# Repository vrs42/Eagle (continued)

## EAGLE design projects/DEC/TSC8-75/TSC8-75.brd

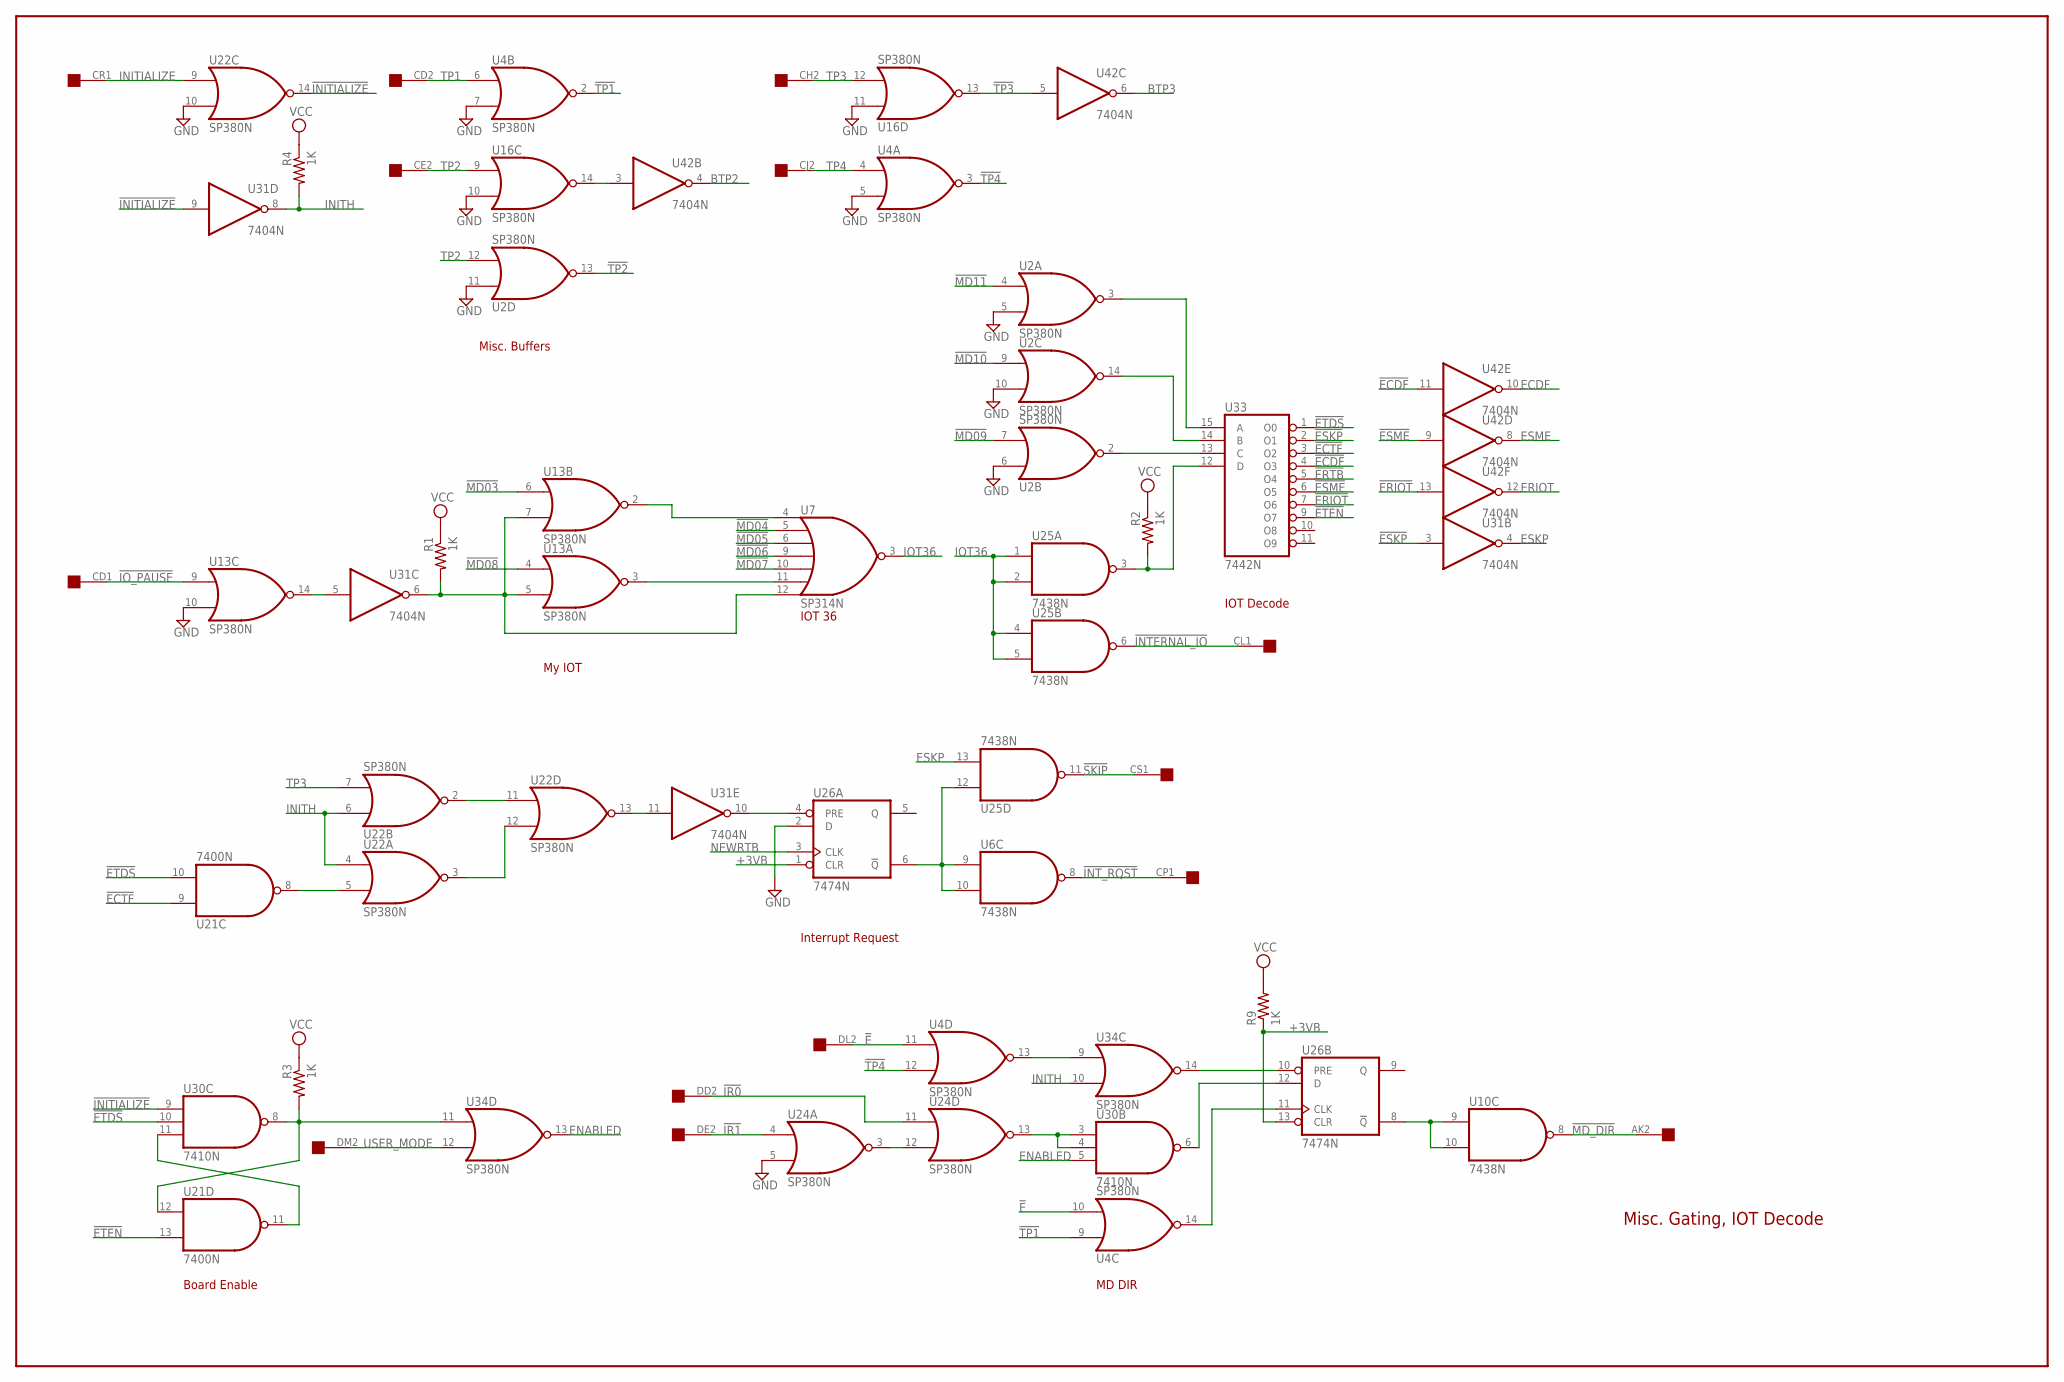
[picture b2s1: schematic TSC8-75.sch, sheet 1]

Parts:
EDGE: edge; EDGE-CON8
R1, R2, R3, R4, R9: 1K; 0204/7
U2, U4, U13, U16, U22, U24, U34: SP380N; DIL14
U6, U10, U25: 7438N; DIL14
U7: SP314N; DIL14
U21: 7400N; DIL14
U26: 7474N; DIL14
U30: 7410N; DIL14
U31, U42: 7404N; DIL14
U33: 7442N; DIL16

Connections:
!E: EDGE.DL2, U4.10 (I1), U4.11 (I0)
!ECDF: U33.4 (O3), U42.11 (I)
!ECTF: U21.9 (I0), U33.3 (O2)
!ERIOT: U33.7 (O6), U42.13 (I); also elsewhere on the board
!ERTB: U33.5 (O4); also elsewhere on the board
!ESKP: U31.3 (I), U33.2 (O1)
!ESME: U33.6 (O5), U42.9 (I)
!ETDS: U21.10 (I1), U30.10 (I1), U33.1 (O0); also elsewhere on the board
!ETEN: U21.13 (I1), U33.9 (O7)
!INITIALIZE: U22.14 (O), U30.9 (I0), U31.9 (I); also elsewhere on the board
!INTERNAL_IO: EDGE.CL1, U25.6 (O)
!INT_RQST: EDGE.CP1, U6.8 (O)
!IO_PAUSE: EDGE.CD1, U13.9 (I0)
!IR0: EDGE.DD2, U24.11 (I0)
!IR1: EDGE.DE2, U24.4 (I0)
!MD03: U13.6 (I0); also elsewhere on the board
!MD04: U7.5 (I1); also elsewhere on the board
!MD05: U7.6 (I2); also elsewhere on the board
!MD06: U7.9 (I3); also elsewhere on the board
!MD07: U7.10 (I4); also elsewhere on the board
!MD08: U13.4 (I0); also elsewhere on the board
!MD09: U2.7 (I1); also elsewhere on the board
!MD10: U2.9 (I0); also elsewhere on the board
!MD11: U2.4 (I0); also elsewhere on the board
!MD_DIR: EDGE.AK2, U10.8 (O)
!SKIP: EDGE.CS1, U25.11 (O); also elsewhere on the board
!TP1: U4.2 (O), U4.9 (I0)
!TP2: U2.13 (O); also elsewhere on the board
!TP3: U16.13 (O), U42.5 (I)
!TP4: U4.3 (O), U4.12 (I1)
+3VB: R9.1, U26.1 (CLR), U26.13 (CLR); also elsewhere on the board
BTP2: U42.4 (O); also elsewhere on the board
BTP3: U42.6 (O); also elsewhere on the board
ECDF: U42.10 (O); also elsewhere on the board
ENABLED: U30.5 (I2), U34.13 (O); also elsewhere on the board
ERIOT: U42.12 (O); also elsewhere on the board
ESKP: U25.13 (I1), U31.4 (O)
ESME: U42.8 (O); also elsewhere on the board
GND: U2.1 (GND), U2.5 (I1), U2.6 (I0), U2.10 (I1), U2.11 (I0), U4.1 (GND), U4.5 (I1), U4.7 (I1), U6.7 (GND), U7.1 (GND), U10.7 (GND), U13.1 (GND), U13.10 (I1), U16.1 (GND), U16.10 (I1), U16.11 (I0), U21.7 (GND), U22.1 (GND), U22.10 (I1), U24.1 (GND), U24.5 (I1), U25.7 (GND), U26.2 (D), U26.7 (GND), U30.7 (GND), U31.7 (GND), U33.8 (GND), U34.1 (GND), U42.7 (GND); also elsewhere on the board
INITH: R4.2, U22.4 (I0), U22.6 (I0), U31.8 (O), U34.10 (I1)
INITIALIZE: EDGE.CR1, U22.9 (I0)
IOT36: U7.3 (O), U25.1 (I0), U25.2 (I1), U25.4 (I0), U25.5 (I1)
IO_PAUSE: U13.14 (O), U31.5 (I)
IR1: U24.3 (O), U24.12 (I1)
IRQ: U6.9 (I0), U6.10 (I1), U25.12 (I0), U26.6 (!Q)
MD09H: U2.2 (O), U33.13 (C)
MD10H: U2.14 (O), U33.14 (B)
MD11H: U2.3 (O), U33.15 (A)
unnamed: U16.14 (O), U42.3 (I)
unnamed: U4.14 (O), U26.11 (CLK)
unnamed: U26.4 (PRE), U31.10 (O)
unnamed: U26.12 (D), U30.6 (O)
unnamed: U26.10 (PRE), U34.14 (O)
unnamed: U7.4 (I0), U13.2 (O)
unnamed: R1.2, U7.12 (I6), U13.5 (I1), U13.7 (I1), U31.6 (O)
unnamed: U7.11 (I5), U13.3 (O)
unnamed: R2.2, U25.3 (O), U33.12 (D)
unnamed: R3.2, U21.12 (I0), U30.8 (O), U34.11 (I0)
unnamed: U4.13 (O), U34.9 (I0)
unnamed: U24.13 (O), U30.3 (I0), U30.4 (I1)
unnamed: U22.2 (O), U22.11 (I0)
unnamed: U22.3 (O), U22.12 (I1)
unnamed: U21.8 (O), U22.5 (I1)
unnamed: U22.13 (O), U31.11 (I)
unnamed: U21.11 (O), U30.11 (I2)
unnamed: U10.9 (I0), U10.10 (I1), U26.8 (!Q)
NEWRTB: U26.3 (CLK); also elsewhere on the board
TP1: EDGE.CD2, U4.6 (I0)
TP2: EDGE.CE2, U2.12 (I1), U16.9 (I0)
TP3: EDGE.CH2, U16.12 (I1), U22.7 (I1)
TP4: EDGE.CJ2, U4.4 (I0)
USER_MODE: EDGE.DM2, U34.12 (I1); also elsewhere on the board
VCC: R1.1, R2.1, R3.1, R4.1, R9.2, U2.8 (VCC), U4.8 (VCC), U6.14 (VCC), U7.8 (VCC), U10.14 (VCC), U13.8 (VCC), U16.8 (VCC), U21.14 (VCC), U22.8 (VCC), U24.8 (VCC), U25.14 (VCC), U26.14 (VCC), U30.14 (VCC), U31.14 (VCC), U33.16 (VCC), U34.8 (VCC), U42.14 (VCC); also elsewhere on the board

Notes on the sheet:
IOT 36
Board Enable
My IOT
IOT Decode
MD DIR
Interrupt Request
Misc. Buffers
Misc. Gating, IOT Decode

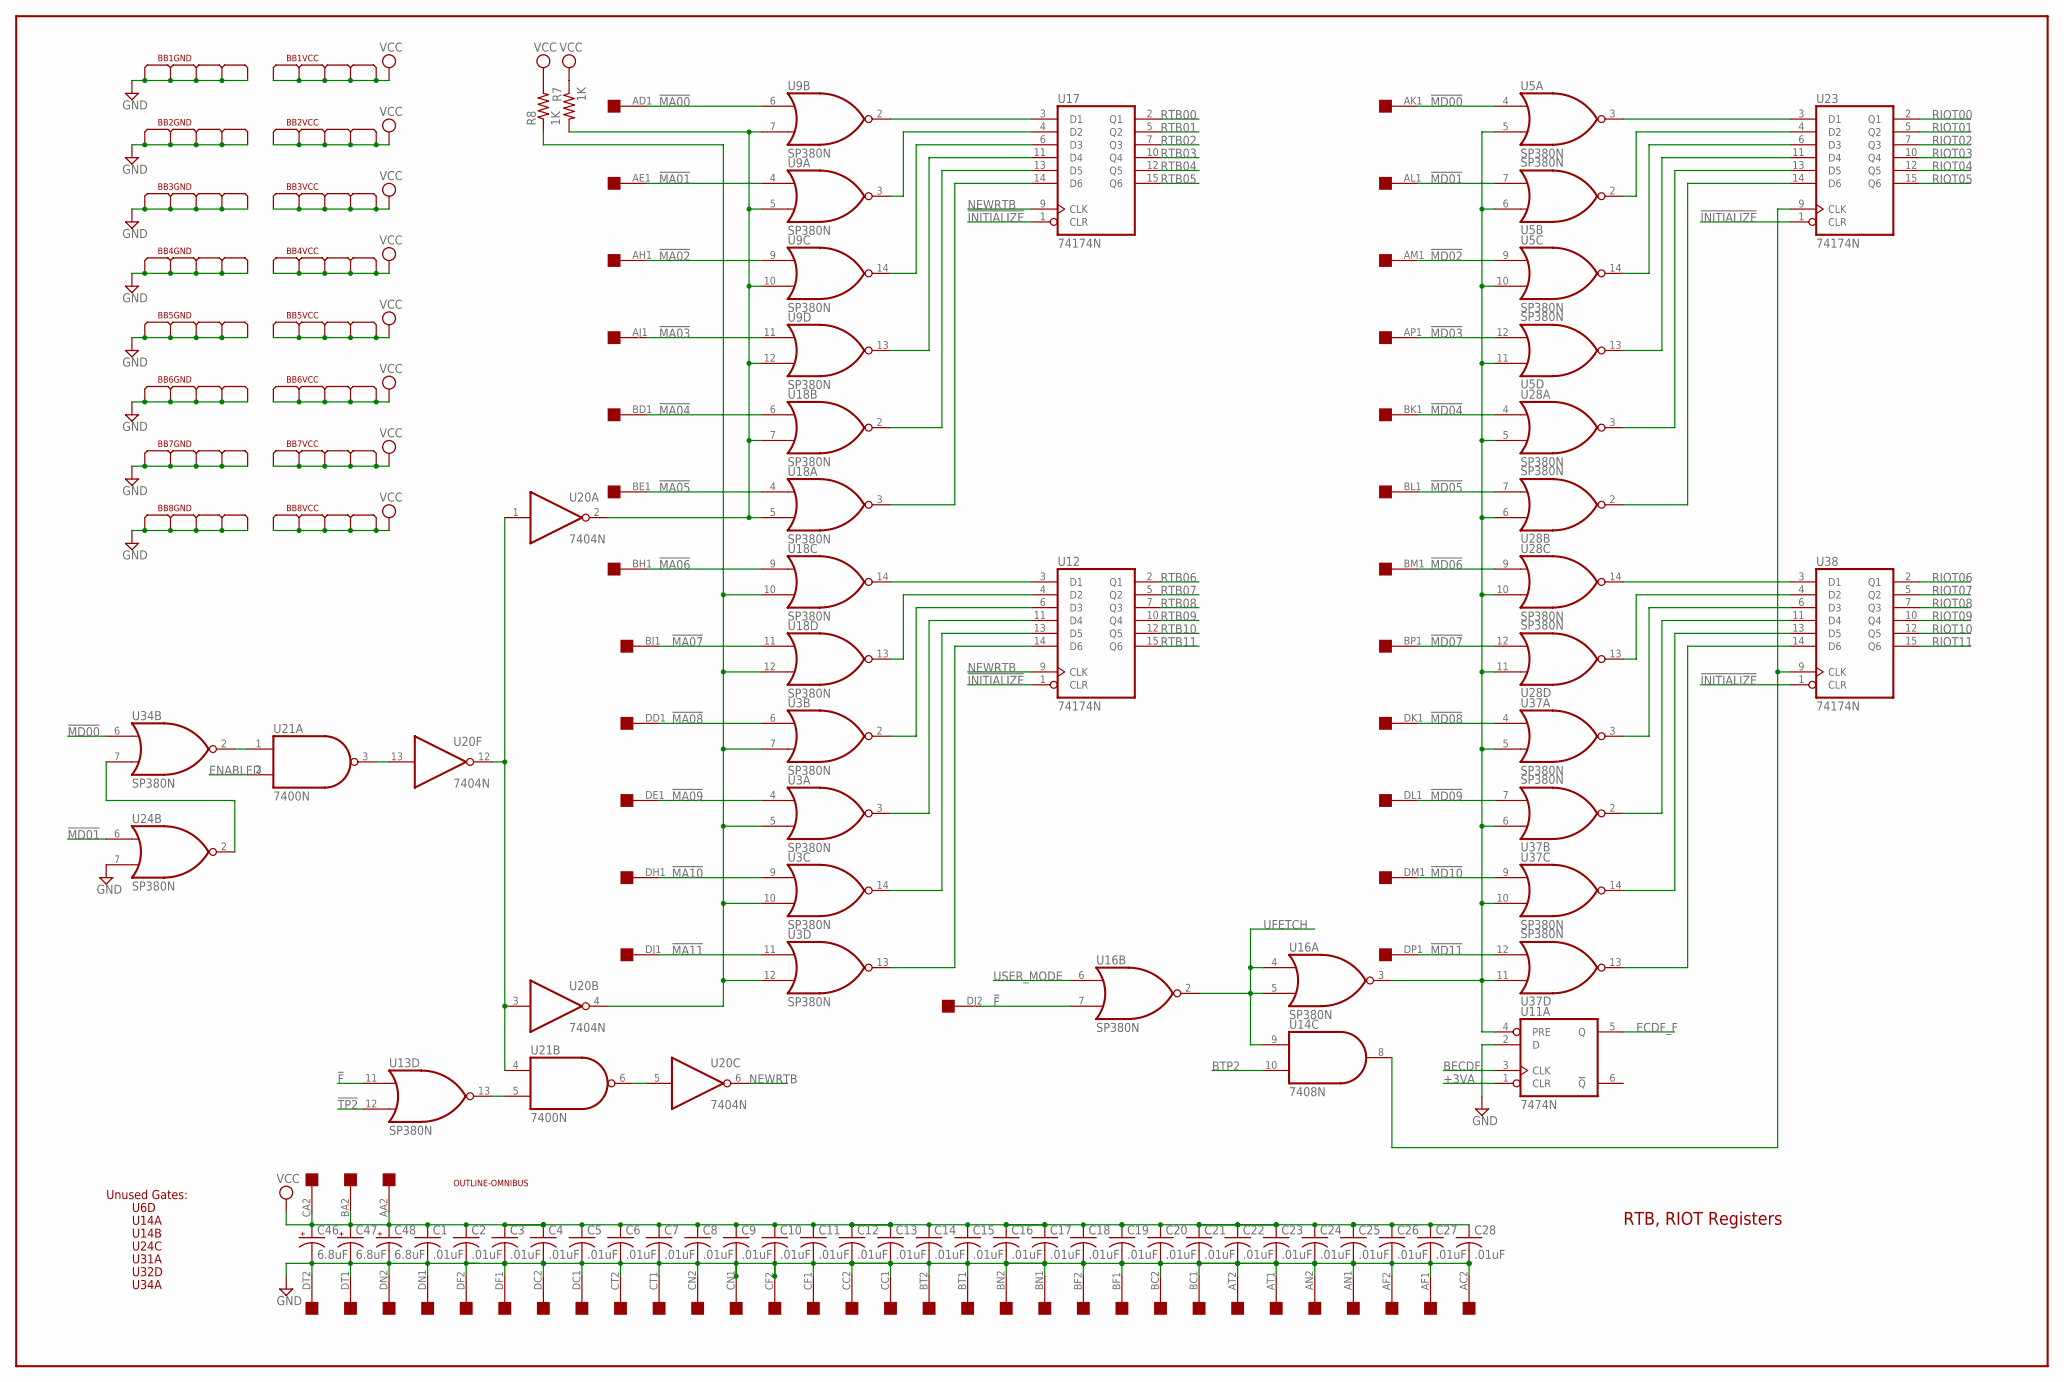
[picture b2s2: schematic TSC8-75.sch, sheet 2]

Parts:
BB1, BB2, BB3, BB4, BB5, BB6, BB7, BB8: BUSBAR
C1, C2, C3, C4, C5, C6, C7, C8, C9, C10, C11, C12, C13, C14, C15, C16, C17, C18, C19, C20, C21, C22, C23, C24, C25, C26, C27, C28: .01uF; C050-025X075
C46, C47, C48: 6.8uF; E12-8
EDGE: edge; EDGE-CON8
R7, R8: 1K; 0204/7
U3, U5, U9, U13, U16, U18, U24, U28, U34, U37: SP380N; DIL14
U11: 7474N; DIL14
U12, U17, U23, U38: 74174N; DIL16
U14: 7408N; DIL14
U20: 7404N; DIL14
U21: 7400N; DIL14
U$1: OUTLINE-OMNIBUS; OMNIBUS

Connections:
!F: EDGE.DJ2, U13.11 (I0), U16.7 (I1)
!INITIALIZE: U12.1 (CLR), U17.1 (CLR), U23.1 (CLR), U38.1 (CLR); also elsewhere on the board
!MA00: EDGE.AD1, U9.6 (I0)
!MA01: EDGE.AE1, U9.4 (I0)
!MA02: EDGE.AH1, U9.9 (I0)
!MA03: EDGE.AJ1, U9.11 (I0)
!MA04: EDGE.BD1, U18.6 (I0)
!MA05: EDGE.BE1, U18.4 (I0)
!MA06: EDGE.BH1, U18.9 (I0)
!MA07: EDGE.BJ1, U18.11 (I0)
!MA08: EDGE.DD1, U3.6 (I0)
!MA09: EDGE.DE1, U3.4 (I0)
!MA10: EDGE.DH1, U3.9 (I0)
!MA11: EDGE.DJ1, U3.11 (I0)
!MD00: EDGE.AK1, U5.4 (I0), U34.6 (I0)
!MD01: EDGE.AL1, U5.7 (I1), U24.6 (I0)
!MD02: EDGE.AM1, U5.9 (I0)
!MD03: EDGE.AP1, U5.12 (I1); also elsewhere on the board
!MD04: EDGE.BK1, U28.4 (I0); also elsewhere on the board
!MD05: EDGE.BL1, U28.7 (I1); also elsewhere on the board
!MD06: EDGE.BM1, U28.9 (I0); also elsewhere on the board
!MD07: EDGE.BP1, U28.12 (I1); also elsewhere on the board
!MD08: EDGE.DK1, U37.4 (I0); also elsewhere on the board
!MD09: EDGE.DL1, U37.7 (I1); also elsewhere on the board
!MD10: EDGE.DM1, U37.9 (I0); also elsewhere on the board
!MD11: EDGE.DP1, U37.12 (I1); also elsewhere on the board
!TP2: U13.12 (I1); also elsewhere on the board
+3VA: U11.1 (CLR); also elsewhere on the board
BECDF: U11.3 (CLK); also elsewhere on the board
BTP2: U14.10 (I1); also elsewhere on the board
ECDF_F: U11.5 (Q); also elsewhere on the board
ENABLED: U21.2 (I1); also elsewhere on the board
GND: BB1.GND1 (1), BB1.GND2 (2), BB1.GND3 (3), BB1.GND4 (4), BB1.GND5 (5), BB2.GND1 (1), BB2.GND2 (2), BB2.GND3 (3), BB2.GND4 (4), BB2.GND5 (5), BB3.GND1 (1), BB3.GND2 (2), BB3.GND3 (3), BB3.GND4 (4), BB3.GND5 (5), BB4.GND1 (1), BB4.GND2 (2), BB4.GND3 (3), BB4.GND4 (4), BB4.GND5 (5), BB5.GND1 (1), BB5.GND2 (2), BB5.GND3 (3), BB5.GND4 (4), BB5.GND5 (5), BB6.GND1 (1), BB6.GND2 (2), BB6.GND3 (3), BB6.GND4 (4), BB6.GND5 (5), BB7.GND1 (1), BB7.GND2 (2), BB7.GND3 (3), BB7.GND4 (4), BB7.GND5 (5), BB8.GND1 (1), BB8.GND2 (2), BB8.GND3 (3), BB8.GND4 (4), BB8.GND5 (5), C1.2, C2.2, C3.2, C4.2, C5.2, C6.2, C7.2, C8.2, C9.2, C10.2, C11.2, C12.2, C13.2, C14.2, C15.2, C16.2, C17.2, C18.2, C19.2, C20.2, C21.2, C22.2, C23.2, C24.2, C25.2, C26.2, C27.2, C28.2, C46.-, C47.-, C48.-, EDGE.AC2, EDGE.AF1, EDGE.AF2, EDGE.AN1, EDGE.AN2, EDGE.AT1, EDGE.AT2, EDGE.BC1, EDGE.BC2, EDGE.BF1, EDGE.BF2, EDGE.BN1, EDGE.BN2, EDGE.BT1, EDGE.BT2, EDGE.CC1, EDGE.CC2, EDGE.CF1, EDGE.CF2, EDGE.CN1, EDGE.CN2, EDGE.CT1, EDGE.CT2, EDGE.DC1, EDGE.DC2, EDGE.DF1, EDGE.DF2, EDGE.DN1, EDGE.DN2, EDGE.DT1, EDGE.DT2, U3.1 (GND), U5.1 (GND), U9.1 (GND), U11.2 (D), U11.7 (GND), U12.8 (GND), U13.1 (GND), U14.7 (GND), U16.1 (GND), U17.8 (GND), U18.1 (GND), U20.7 (GND), U21.7 (GND), U23.8 (GND), U24.1 (GND), U24.7 (I1), U28.1 (GND), U34.1 (GND), U37.1 (GND), U38.8 (GND); also elsewhere on the board
MD01H: U24.2 (O), U34.7 (I1)
unnamed: U20.5 (I), U21.6 (O)
unnamed: U9.3 (O), U17.4 (D2)
unnamed: R7.2, U9.5 (I1), U9.7 (I1), U9.10 (I1), U9.12 (I1), U18.5 (I1), U18.7 (I1), U20.2 (O)
unnamed: U9.13 (O), U17.11 (D4)
unnamed: U9.14 (O), U17.6 (D3)
unnamed: U9.2 (O), U17.3 (D1)
unnamed: U17.13 (D5), U18.2 (O)
unnamed: R8.1, U3.5 (I1), U3.7 (I1), U3.10 (I1), U3.12 (I1), U18.10 (I1), U18.12 (I1), U20.4 (O)
unnamed: U12.4 (D2), U18.13 (O)
unnamed: U12.3 (D1), U18.14 (O)
unnamed: U17.14 (D6), U18.3 (O)
unnamed: U37.3 (O), U38.6 (D3)
unnamed: U21.1 (I0), U34.2 (O)
unnamed: U14.8 (O), U23.9 (CLK), U38.9 (CLK)
unnamed: U5.3 (O), U23.3 (D1)
unnamed: U5.5 (I1), U5.6 (I0), U5.10 (I1), U5.11 (I0), U11.4 (PRE), U16.3 (O), U28.5 (I1), U28.6 (I0), U28.10 (I1), U28.11 (I0), U37.5 (I1), U37.6 (I0), U37.10 (I1), U37.11 (I0)
unnamed: U5.13 (O), U23.11 (D4)
unnamed: U5.14 (O), U23.6 (D3)
unnamed: U5.2 (O), U23.4 (D2)
unnamed: U23.14 (D6), U28.2 (O)
unnamed: U23.13 (D5), U28.3 (O)
unnamed: U13.13 (O), U21.5 (I1)
unnamed: U3.3 (O), U12.11 (D4)
unnamed: U3.13 (O), U12.14 (D6)
unnamed: U3.14 (O), U12.13 (D5)
unnamed: U3.2 (O), U12.6 (D3)
unnamed: U20.1 (I), U20.3 (I), U20.12 (O), U21.4 (I0)
unnamed: U20.13 (I), U21.3 (O)
unnamed: U28.14 (O), U38.3 (D1)
unnamed: U37.13 (O), U38.14 (D6)
unnamed: U37.14 (O), U38.13 (D5)
unnamed: U37.2 (O), U38.11 (D4)
unnamed: U28.13 (O), U38.4 (D2)
NEWRTB: U12.9 (CLK), U17.9 (CLK), U20.6 (O); also elsewhere on the board
RIOT00: U23.2 (Q1); also elsewhere on the board
RIOT01: U23.5 (Q2); also elsewhere on the board
RIOT02: U23.7 (Q3); also elsewhere on the board
RIOT03: U23.10 (Q4); also elsewhere on the board
RIOT04: U23.12 (Q5); also elsewhere on the board
RIOT05: U23.15 (Q6); also elsewhere on the board
RIOT06: U38.2 (Q1); also elsewhere on the board
RIOT07: U38.5 (Q2); also elsewhere on the board
RIOT08: U38.7 (Q3); also elsewhere on the board
RIOT09: U38.10 (Q4); also elsewhere on the board
RIOT10: U38.12 (Q5); also elsewhere on the board
RIOT11: U38.15 (Q6); also elsewhere on the board
RTB00: U17.2 (Q1); also elsewhere on the board
RTB01: U17.5 (Q2); also elsewhere on the board
RTB02: U17.7 (Q3); also elsewhere on the board
RTB03: U17.10 (Q4); also elsewhere on the board
RTB04: U17.12 (Q5); also elsewhere on the board
RTB05: U17.15 (Q6); also elsewhere on the board
RTB06: U12.2 (Q1); also elsewhere on the board
RTB07: U12.5 (Q2); also elsewhere on the board
RTB08: U12.7 (Q3); also elsewhere on the board
RTB09: U12.10 (Q4); also elsewhere on the board
RTB10: U12.12 (Q5); also elsewhere on the board
RTB11: U12.15 (Q6); also elsewhere on the board
UFETCH: U14.9 (I0), U16.2 (O), U16.4 (I0), U16.5 (I1); also elsewhere on the board
USER_MODE: U16.6 (I0); also elsewhere on the board
VCC: BB1.VCC1 (1), BB1.VCC2 (2), BB1.VCC3 (3), BB1.VCC4 (4), BB1.VCC5 (5), BB2.VCC1 (1), BB2.VCC2 (2), BB2.VCC3 (3), BB2.VCC4 (4), BB2.VCC5 (5), BB3.VCC1 (1), BB3.VCC2 (2), BB3.VCC3 (3), BB3.VCC4 (4), BB3.VCC5 (5), BB4.VCC1 (1), BB4.VCC2 (2), BB4.VCC3 (3), BB4.VCC4 (4), BB4.VCC5 (5), BB5.VCC1 (1), BB5.VCC2 (2), BB5.VCC3 (3), BB5.VCC4 (4), BB5.VCC5 (5), BB6.VCC1 (1), BB6.VCC2 (2), BB6.VCC3 (3), BB6.VCC4 (4), BB6.VCC5 (5), BB7.VCC1 (1), BB7.VCC2 (2), BB7.VCC3 (3), BB7.VCC4 (4), BB7.VCC5 (5), BB8.VCC1 (1), BB8.VCC2 (2), BB8.VCC3 (3), BB8.VCC4 (4), BB8.VCC5 (5), C1.1, C2.1, C3.1, C4.1, C5.1, C6.1, C7.1, C8.1, C9.1, C10.1, C11.1, C12.1, C13.1, C14.1, C15.1, C16.1, C17.1, C18.1, C19.1, C20.1, C21.1, C22.1, C23.1, C24.1, C25.1, C26.1, C27.1, C28.1, C46.+, C47.+, C48.+, EDGE.AA2, EDGE.BA2, EDGE.CA2, R7.1, R8.2, U3.8 (VCC), U5.8 (VCC), U9.8 (VCC), U11.14 (VCC), U12.16 (VCC), U13.8 (VCC), U14.14 (VCC), U16.8 (VCC), U17.16 (VCC), U18.8 (VCC), U20.14 (VCC), U21.14 (VCC), U23.16 (VCC), U24.8 (VCC), U28.8 (VCC), U34.8 (VCC), U37.8 (VCC), U38.16 (VCC); also elsewhere on the board

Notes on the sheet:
Unused Gates:
U24C
U6D
U14A
U14B
U31A
U32D
U34A
RTB, RIOT Registers

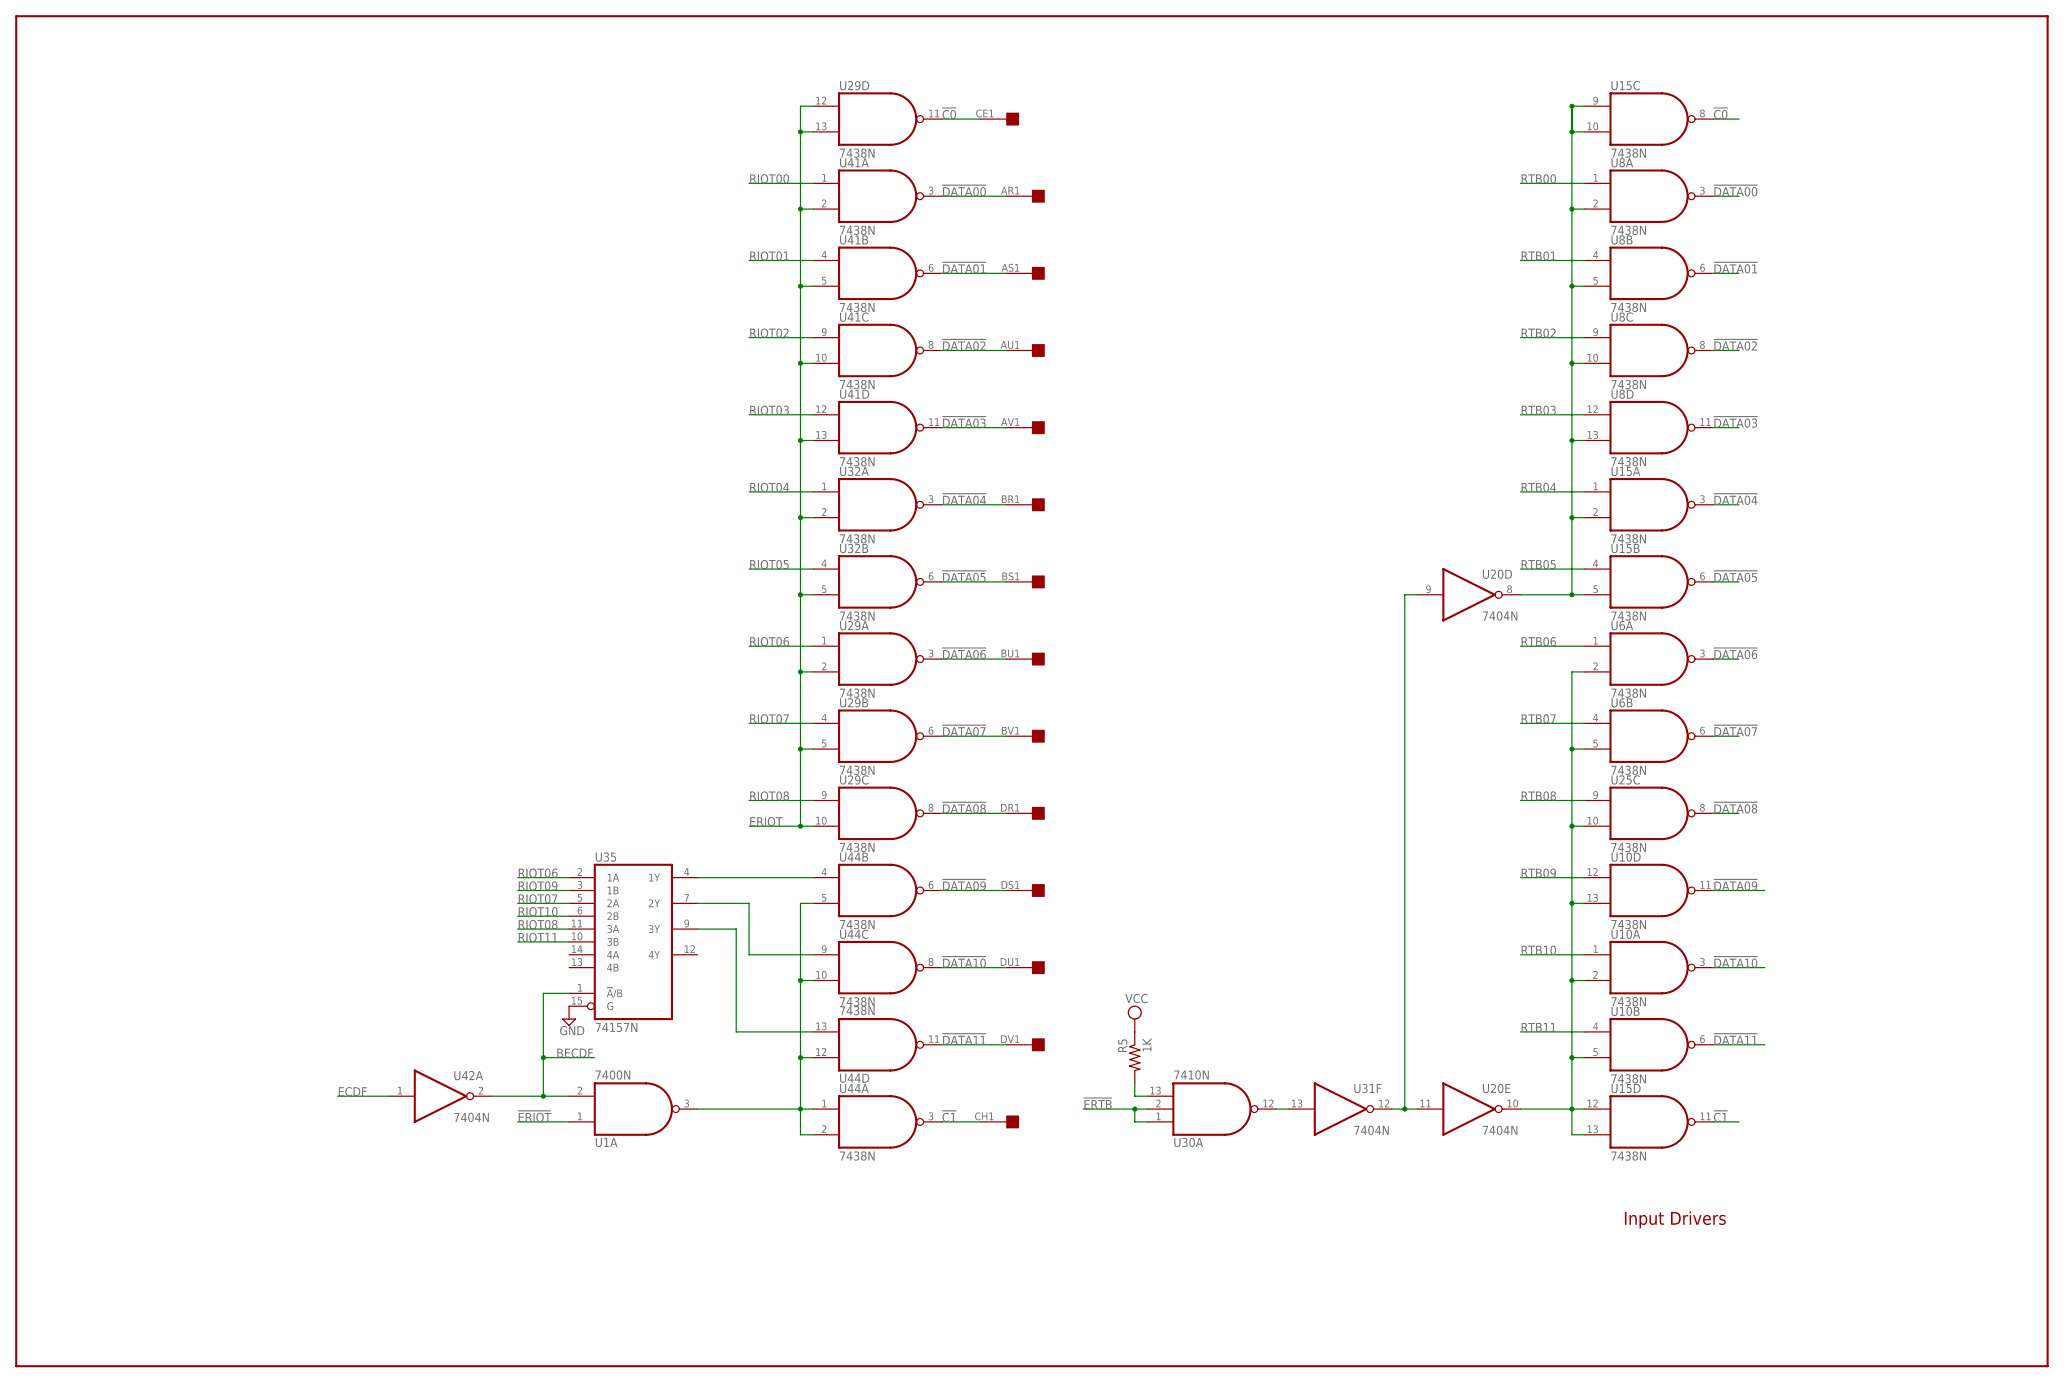
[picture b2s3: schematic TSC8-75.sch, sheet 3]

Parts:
EDGE: edge; EDGE-CON8
R5: 1K; 0204/7
U1: 7400N; DIL14
U6, U8, U10, U15, U25, U29, U32, U41, U44: 7438N; DIL14
U20, U31, U42: 7404N; DIL14
U30: 7410N; DIL14
U35: 74157N; DIL16

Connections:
!C0: EDGE.CE1, U15.8 (O), U29.11 (O)
!C1: EDGE.CH1, U15.11 (O), U44.3 (O)
!DATA00: EDGE.AR1, U8.3 (O), U41.3 (O)
!DATA01: EDGE.AS1, U8.6 (O), U41.6 (O)
!DATA02: EDGE.AU1, U8.8 (O), U41.8 (O)
!DATA03: EDGE.AV1, U8.11 (O), U41.11 (O)
!DATA04: EDGE.BR1, U15.3 (O), U32.3 (O)
!DATA05: EDGE.BS1, U15.6 (O), U32.6 (O)
!DATA06: EDGE.BU1, U6.3 (O), U29.3 (O)
!DATA07: EDGE.BV1, U6.6 (O), U29.6 (O)
!DATA08: EDGE.DR1, U25.8 (O), U29.8 (O)
!DATA09: EDGE.DS1, U10.11 (O), U44.6 (O)
!DATA10: EDGE.DU1, U10.3 (O), U44.8 (O)
!DATA11: EDGE.DV1, U10.6 (O), U44.11 (O)
!ERIOT: U1.1 (I0); also elsewhere on the board
!ERTB: U30.1 (I0), U30.2 (I1); also elsewhere on the board
BECDF: U1.2 (I1), U35.1 (!A!/B), U42.2 (O); also elsewhere on the board
ECDF: U42.1 (I); also elsewhere on the board
ERIOT: U29.2 (I1), U29.5 (I1), U29.10 (I1), U29.12 (I0), U29.13 (I1), U32.2 (I1), U32.5 (I1), U41.2 (I1), U41.5 (I1), U41.10 (I1), U41.13 (I1); also elsewhere on the board
GND: U1.7 (GND), U6.7 (GND), U8.7 (GND), U10.7 (GND), U15.7 (GND), U20.7 (GND), U25.7 (GND), U29.7 (GND), U30.7 (GND), U31.7 (GND), U32.7 (GND), U35.8 (GND), U35.15 (G), U41.7 (GND), U42.7 (GND), U44.7 (GND); also elsewhere on the board
unnamed: U8.2 (I1), U8.5 (I1), U8.10 (I1), U8.13 (I1), U15.2 (I1), U15.5 (I1), U15.9 (I0), U15.10 (I1), U20.8 (O)
unnamed: U35.4 (1Y), U44.4 (I0)
unnamed: U35.9 (3Y), U44.13 (I1)
unnamed: U35.7 (2Y), U44.9 (I0)
unnamed: U1.3 (O), U44.1 (I0), U44.2 (I1), U44.5 (I1), U44.10 (I1), U44.12 (I0)
unnamed: U6.2 (I1), U6.5 (I1), U10.2 (I1), U10.5 (I1), U10.13 (I1), U15.12 (I0), U15.13 (I1), U20.10 (O), U25.10 (I1)
unnamed: U30.12 (O), U31.13 (I)
unnamed: U20.9 (I), U20.11 (I), U31.12 (O)
unnamed: R5.2, U30.13 (I2)
RIOT00: U41.1 (I0); also elsewhere on the board
RIOT01: U41.4 (I0); also elsewhere on the board
RIOT02: U41.9 (I0); also elsewhere on the board
RIOT03: U41.12 (I0); also elsewhere on the board
RIOT04: U32.1 (I0); also elsewhere on the board
RIOT05: U32.4 (I0); also elsewhere on the board
RIOT06: U29.1 (I0), U35.2 (1A); also elsewhere on the board
RIOT07: U29.4 (I0), U35.5 (2A); also elsewhere on the board
RIOT08: U29.9 (I0), U35.11 (3A); also elsewhere on the board
RIOT09: U35.3 (1B); also elsewhere on the board
RIOT10: U35.6 (2B); also elsewhere on the board
RIOT11: U35.10 (3B); also elsewhere on the board
RTB00: U8.1 (I0); also elsewhere on the board
RTB01: U8.4 (I0); also elsewhere on the board
RTB02: U8.9 (I0); also elsewhere on the board
RTB03: U8.12 (I0); also elsewhere on the board
RTB04: U15.1 (I0); also elsewhere on the board
RTB05: U15.4 (I0); also elsewhere on the board
RTB06: U6.1 (I0); also elsewhere on the board
RTB07: U6.4 (I0); also elsewhere on the board
RTB08: U25.9 (I0); also elsewhere on the board
RTB09: U10.12 (I0); also elsewhere on the board
RTB10: U10.1 (I0); also elsewhere on the board
RTB11: U10.4 (I0); also elsewhere on the board
VCC: R5.1, U1.14 (VCC), U6.14 (VCC), U8.14 (VCC), U10.14 (VCC), U15.14 (VCC), U20.14 (VCC), U25.14 (VCC), U29.14 (VCC), U30.14 (VCC), U31.14 (VCC), U32.14 (VCC), U35.16 (VCC), U41.14 (VCC), U42.14 (VCC), U44.14 (VCC); also elsewhere on the board

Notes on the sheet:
Input Drivers

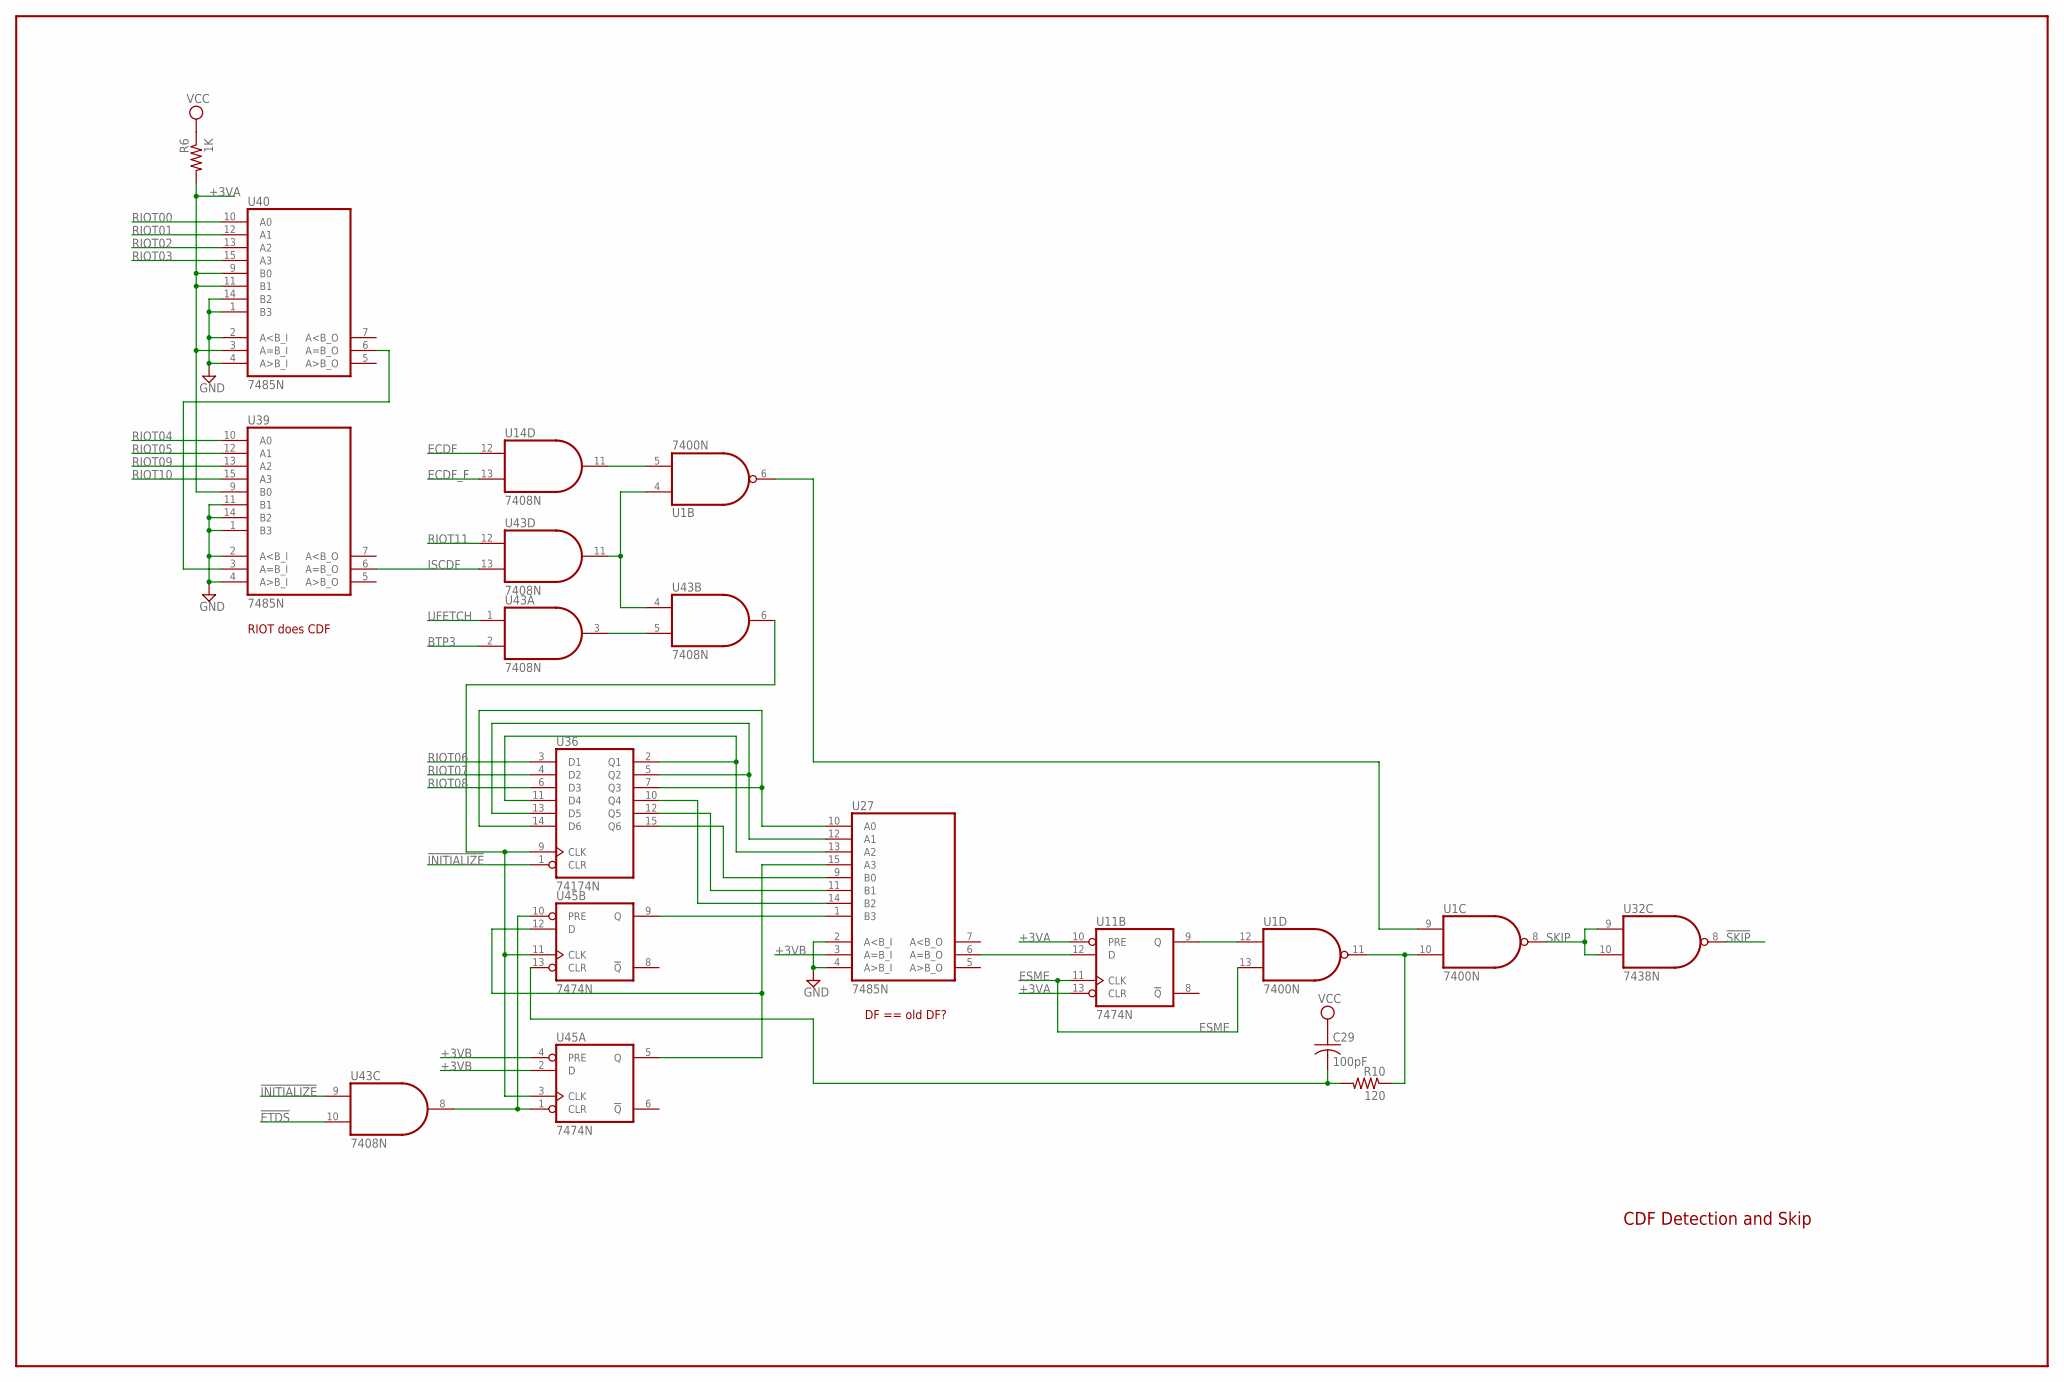
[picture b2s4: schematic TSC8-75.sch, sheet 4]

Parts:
C29: 100pF; C050-025X075
R6: 1K; 0204/7
R10: 120; 0204/7
U1: 7400N; DIL14
U11, U45: 7474N; DIL14
U14, U43: 7408N; DIL14
U27, U39, U40: 7485N; DIL16
U32: 7438N; DIL14
U36: 74174N; DIL16

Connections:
!ETDS: U43.10 (I1); also elsewhere on the board
!INITIALIZE: U36.1 (CLR), U43.9 (I0); also elsewhere on the board
!SKIP: U32.8 (O); also elsewhere on the board
+3VA: R6.2, U11.10 (PRE), U11.13 (CLR), U39.9 (B0), U40.3 (A=B_I), U40.9 (B0), U40.11 (B1); also elsewhere on the board
+3VB: U27.3 (A=B_I), U45.2 (D), U45.4 (PRE); also elsewhere on the board
BTP3: U43.2 (I1); also elsewhere on the board
ECDF: U14.12 (I0); also elsewhere on the board
ECDF_F: U14.13 (I1); also elsewhere on the board
ESME: U1.13 (I1), U11.11 (CLK); also elsewhere on the board
GND: U1.7 (GND), U11.7 (GND), U14.7 (GND), U27.2 (A<B_I), U27.4 (A>B_I), U27.8 (GND), U32.7 (GND), U36.8 (GND), U39.1 (B3), U39.2 (A<B_I), U39.4 (A>B_I), U39.8 (GND), U39.11 (B1), U39.14 (B2), U40.1 (B3), U40.2 (A<B_I), U40.4 (A>B_I), U40.8 (GND), U40.14 (B2), U43.7 (GND), U45.7 (GND); also elsewhere on the board
ISCDF: U39.6 (A=B_O), U43.13 (I1)
unnamed: U1.5 (I1), U14.11 (O)
unnamed: U11.12 (D), U27.6 (A=B_O)
unnamed: U27.10 (A0), U36.7 (Q3), U36.14 (D6)
unnamed: U27.1 (B3), U45.9 (Q)
unnamed: U27.14 (B2), U36.10 (Q4)
unnamed: U27.11 (B1), U36.12 (Q5)
unnamed: U27.9 (B0), U36.15 (Q6)
unnamed: U27.15 (A3), U45.5 (Q), U45.12 (D)
unnamed: U27.13 (A2), U36.2 (Q1), U36.11 (D4)
unnamed: U27.12 (A1), U36.5 (Q2), U36.13 (D5)
unnamed: U36.9 (CLK), U43.6 (O), U45.3 (CLK), U45.11 (CLK)
unnamed: C29.2, R10.2, U45.13 (CLR)
unnamed: U43.8 (O), U45.1 (CLR), U45.10 (PRE)
unnamed: R10.1, U1.10 (I1), U1.11 (O)
unnamed: U1.4 (I0), U43.4 (I0), U43.11 (O)
unnamed: U43.3 (O), U43.5 (I1)
unnamed: U39.3 (A=B_I), U40.6 (A=B_O)
unnamed: U1.12 (I0), U11.9 (Q)
unnamed: U1.6 (O), U1.9 (I0)
RIOT00: U40.10 (A0); also elsewhere on the board
RIOT01: U40.12 (A1); also elsewhere on the board
RIOT02: U40.13 (A2); also elsewhere on the board
RIOT03: U40.15 (A3); also elsewhere on the board
RIOT04: U39.10 (A0); also elsewhere on the board
RIOT05: U39.12 (A1); also elsewhere on the board
RIOT06: U36.3 (D1); also elsewhere on the board
RIOT07: U36.4 (D2); also elsewhere on the board
RIOT08: U36.6 (D3); also elsewhere on the board
RIOT09: U39.13 (A2); also elsewhere on the board
RIOT10: U39.15 (A3); also elsewhere on the board
RIOT11: U43.12 (I0); also elsewhere on the board
SKIP: U1.8 (O), U32.9 (I0), U32.10 (I1)
UFETCH: U43.1 (I0); also elsewhere on the board
VCC: C29.1, R6.1, U1.14 (VCC), U11.14 (VCC), U14.14 (VCC), U27.16 (VCC), U32.14 (VCC), U36.16 (VCC), U39.16 (VCC), U40.16 (VCC), U43.14 (VCC), U45.14 (VCC); also elsewhere on the board

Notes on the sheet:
RIOT does CDF
DF == old DF?
CDF Detection and Skip

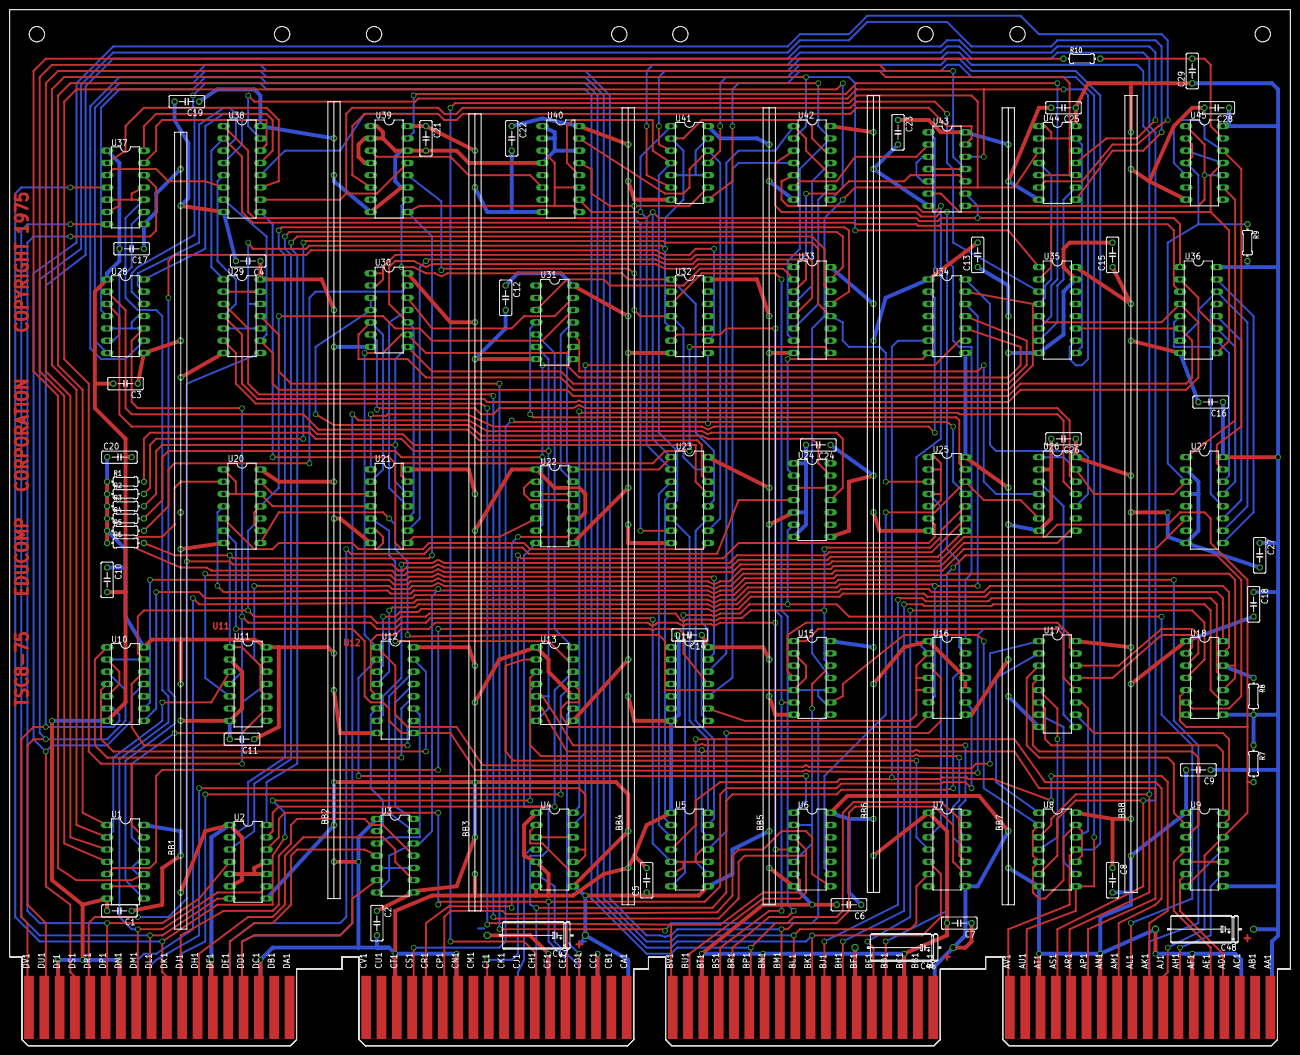
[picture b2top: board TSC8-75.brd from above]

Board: 3 copper layers, 265.3 x 214.6 mm, 96 parts (0 on the bottom side), 195 nets.
